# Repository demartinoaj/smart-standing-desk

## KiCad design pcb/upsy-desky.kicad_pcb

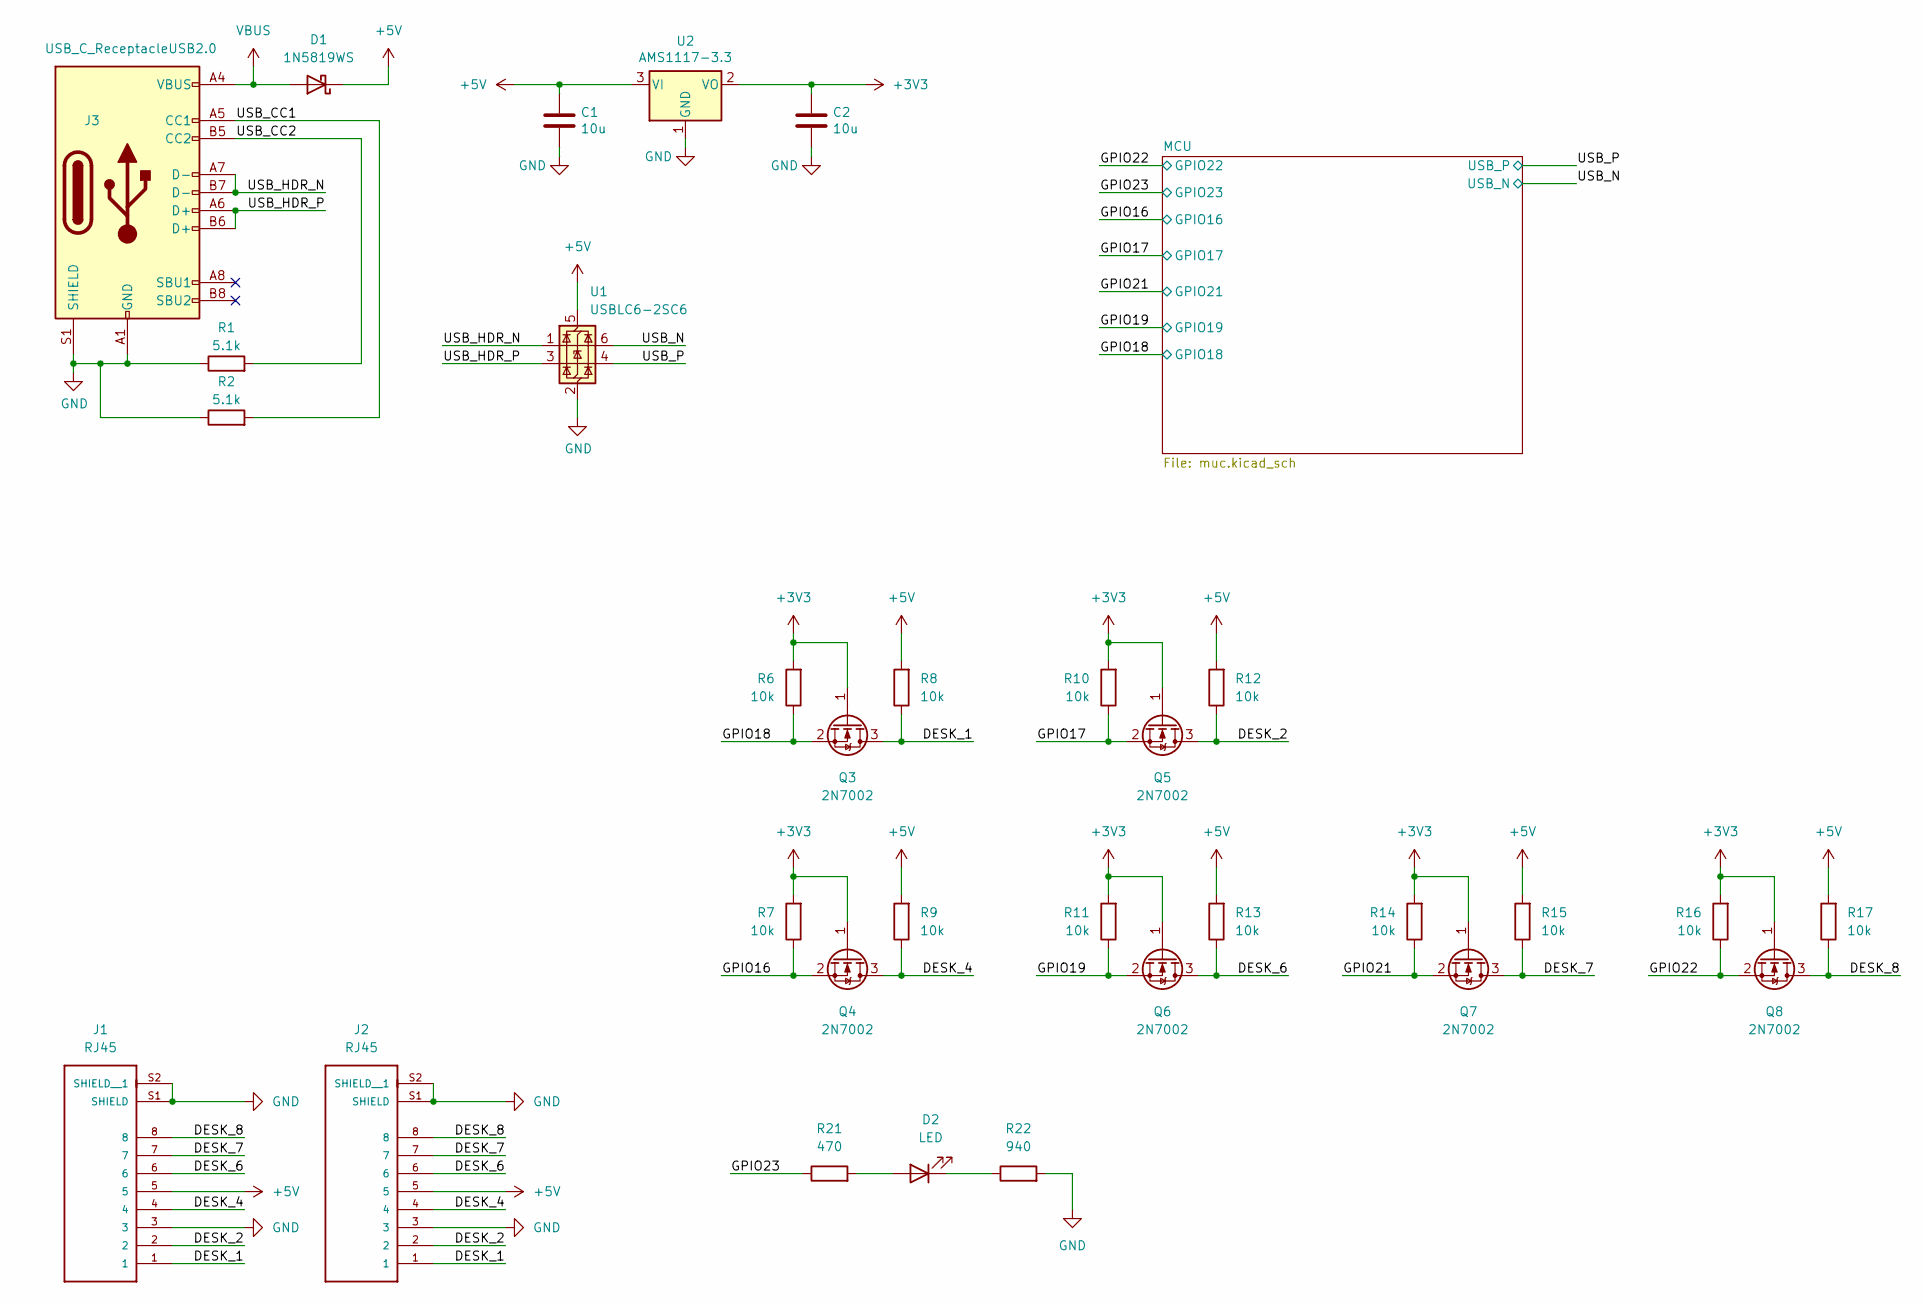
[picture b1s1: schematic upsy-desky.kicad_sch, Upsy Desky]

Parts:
C1, C2: 10u; C_0402_1005Metric; MPN GRM155R60J106ME05J; LCSC C15525
D1: 1N5819WS; D_SOD-323; MPN 1N5819WS; LCSC C191023
D2: LED; LED_0603_1608Metric; MPN LTST-C190KRKT; LCSC C2286
J1, J2: RJ45; ASSMANN_A-2004-2-4-LPS-N-R; PARTREV 00; LCSC C708595
J3: USB_C_ReceptacleUSB2.0; USB_C_Receptacle_Palconn_UTC16-G; MPN TYPE-C-31-M-12; LCSC C165948
Q3, Q4, Q5, Q6, Q7, Q8: 2N7002; SOT-23; MPN 2N7002; LCSC C8545
R1, R2: 5.1k; R_0402_1005Metric; MPN RC0402JR-075R1L; LCSC C25905
R6, R7, R8, R9, R10, R11, R12, R13, R14, R15, R16, R17: 10k; R_0402_1005Metric; MPN RC0402JR-1310KL; LCSC C25744
R21: 470; R_0402_1005Metric; MPN RC1005J471CS; LCSC C25117
R22: 940; R_0402_1005Metric; MPN RMCF0402FT953R; LCSC C11702
U1: USBLC6-2SC6; SOT-23-6
U2: AMS1117-3.3; SOT-223-3_TabPin2; MPN AMS1117-3.3; LCSC C6186

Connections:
+3V3: C2.1, Q3.1 (G), Q4.1 (G), Q5.1 (G), Q6.1 (G), Q7.1 (G), Q8.1 (G), R6.2, R7.2, R10.2, R11.2, R14.2, R16.2, U2.2 (VO); also elsewhere on the board
+5V: C1.1, D1.1 (K), J1.5, J2.5, R8.2, R9.2, R12.2, R13.2, R15.2, R17.2, U1.5 (VBUS), U2.3 (VI)
/DESK_1: J1.1, J2.1, Q3.3 (D), R8.1
/DESK_2: J1.2, J2.2, Q5.3 (D), R12.1
/DESK_4: J1.4, J2.4, Q4.3 (D), R9.1
/DESK_6: J1.6, J2.6, Q6.3 (D), R13.1
/DESK_7: J1.7, J2.7, Q7.3 (D), R15.1
/DESK_8: J1.8, J2.8, Q8.3 (D), R17.1
/GPIO16: Q4.2 (S), R7.1; also elsewhere on the board
/GPIO17: Q5.2 (S), R10.1; also elsewhere on the board
/GPIO18: Q3.2 (S), R6.1; also elsewhere on the board
/GPIO19: Q6.2 (S), R11.1; also elsewhere on the board
/GPIO21: Q7.2 (S), R14.1; also elsewhere on the board
/GPIO22: Q8.2 (S), R16.1; also elsewhere on the board
/GPIO23: R21.1; also elsewhere on the board
/USB_CC1: J3.A5 (CC1), R2.2
/USB_CC2: J3.B5 (CC2), R1.2
/USB_HDR_N: J3.A7 (D-), J3.B7 (D-), U1.1 (I/O1)
/USB_HDR_P: J3.A6 (D+), J3.B6 (D+), U1.3 (I/O2)
/USB_N: U1.6 (I/O1); also elsewhere on the board
/USB_P: U1.4 (I/O2); also elsewhere on the board
GND: C1.2, C2.2, J1.3, J1.S1 (SHIELD), J1.S2 (SHIELD__1), J2.3, J2.S1 (SHIELD), J2.S2 (SHIELD__1), J3.A1 (GND), J3.A12 (GND), J3.B1 (GND), J3.B12 (GND), J3.S1 (SHIELD), R1.1, R2.1, R22.2, U1.2 (GND), U2.1 (GND); also elsewhere on the board
unnamed: D2.2 (A), R21.2
unnamed: D2.1 (K), R22.1
VBUS: D1.2 (A), J3.A4 (VBUS), J3.A9 (VBUS), J3.B4 (VBUS), J3.B9 (VBUS)

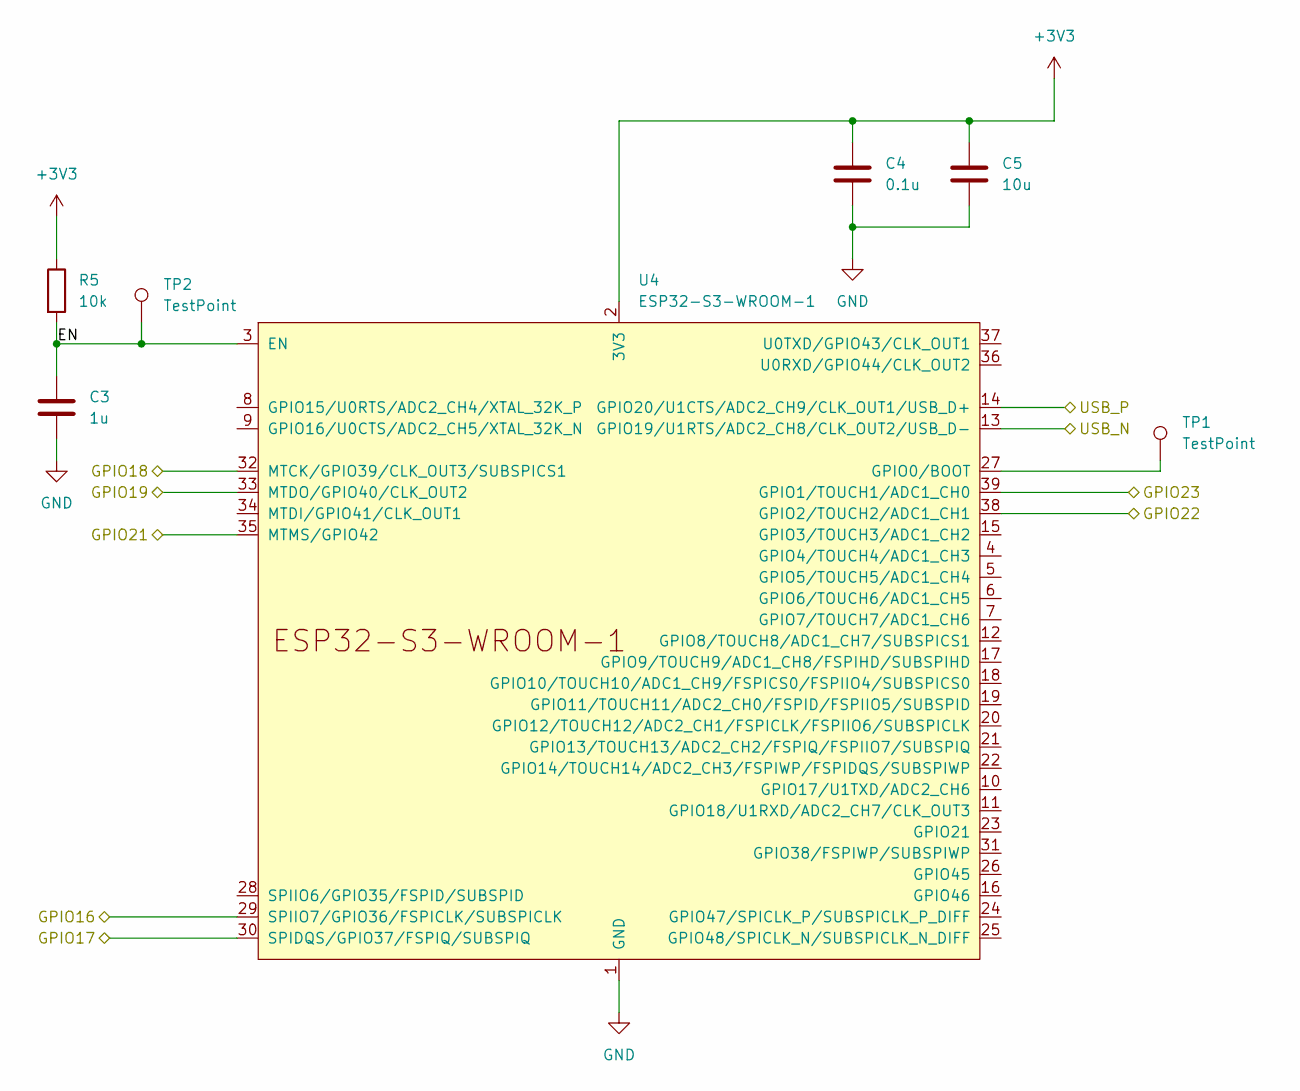
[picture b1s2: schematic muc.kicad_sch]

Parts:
C3: 1u; C_0402_1005Metric; MPN 0402W105K100HI; LCSC C52923
C4: 0.1u; C_0402_1005Metric; MPN 0402B104K160HI; LCSC C1525
C5: 10u; C_0402_1005Metric; MPN GRM155R60J106ME05J; LCSC C15525
R5: 10k; R_0402_1005Metric; MPN RC0402JR-1310KL; LCSC C25744
TP1, TP2: TestPoint; TestPoint_Loop_D1.80mm_Drill1.0mm_Beaded
U4: ESP32-S3-WROOM-1

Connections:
+3V3: C4.1, C5.1, R5.1, U4.2 (3V3); also elsewhere on the board
/GPIO16: U4.29 (SPIIO7/GPIO36/FSPICLK/SUBSPICLK); also elsewhere on the board
/GPIO17: U4.30 (SPIDQS/GPIO37/FSPIQ/SUBSPIQ); also elsewhere on the board
/GPIO18: U4.32 (MTCK/GPIO39/CLK_OUT3/SUBSPICS1); also elsewhere on the board
/GPIO19: U4.33 (MTDO/GPIO40/CLK_OUT2); also elsewhere on the board
/GPIO21: U4.35 (MTMS/GPIO42); also elsewhere on the board
/GPIO22: U4.38 (GPIO2/TOUCH2/ADC1_CH1); also elsewhere on the board
/GPIO23: U4.39 (GPIO1/TOUCH1/ADC1_CH0); also elsewhere on the board
/MCU/EN: C3.1, R5.2, TP2.1, U4.3 (EN)
/USB_N: U4.13 (GPIO19/U1RTS/ADC2_CH8/CLK_OUT2/USB_D-); also elsewhere on the board
/USB_P: U4.14 (GPIO20/U1CTS/ADC2_CH9/CLK_OUT1/USB_D+); also elsewhere on the board
GND: C3.2, C4.2, C5.2, U4.1 (GND), U4.40 (GND), U4.41 (GND); also elsewhere on the board
unnamed: TP1.1, U4.27 (GPIO0/BOOT)

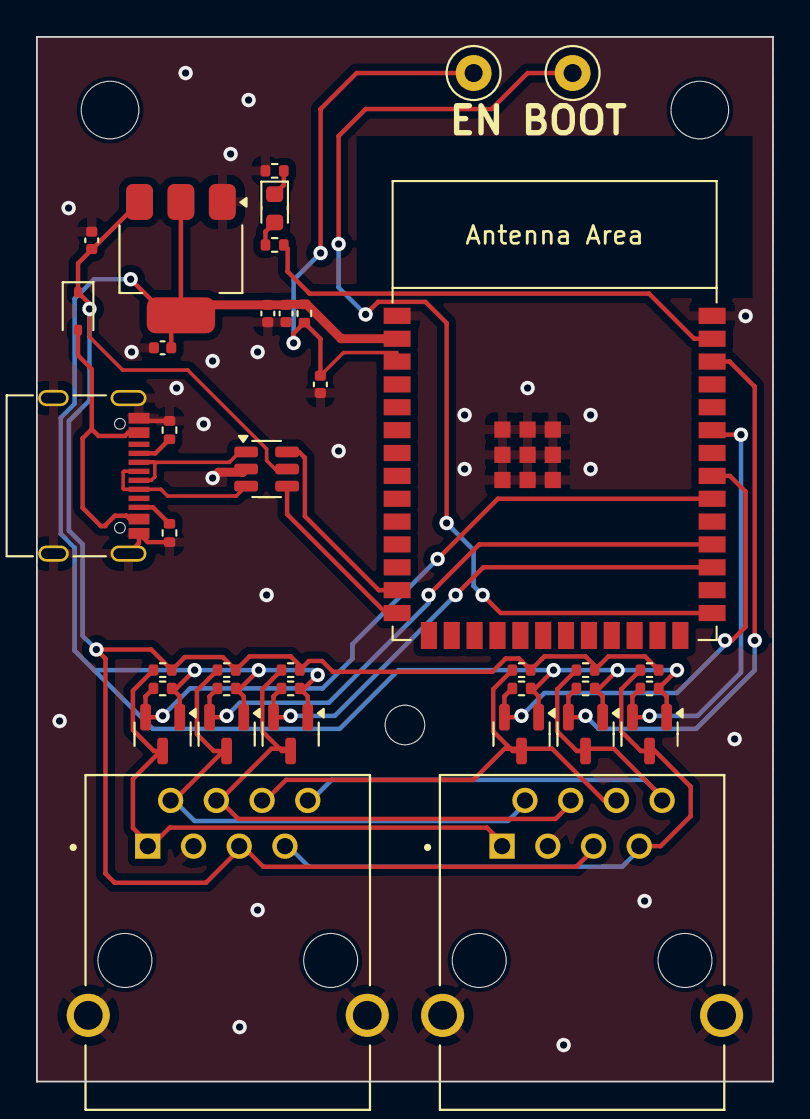
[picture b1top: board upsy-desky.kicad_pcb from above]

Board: 2 copper layers, 40.9 x 58.0 mm, 38 parts (0 on the bottom side), 27 nets.

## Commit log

2025-05-04 Adding updated PCB files using ESP32-s3-WROOM-1 MCU, removed UART to USB logic
